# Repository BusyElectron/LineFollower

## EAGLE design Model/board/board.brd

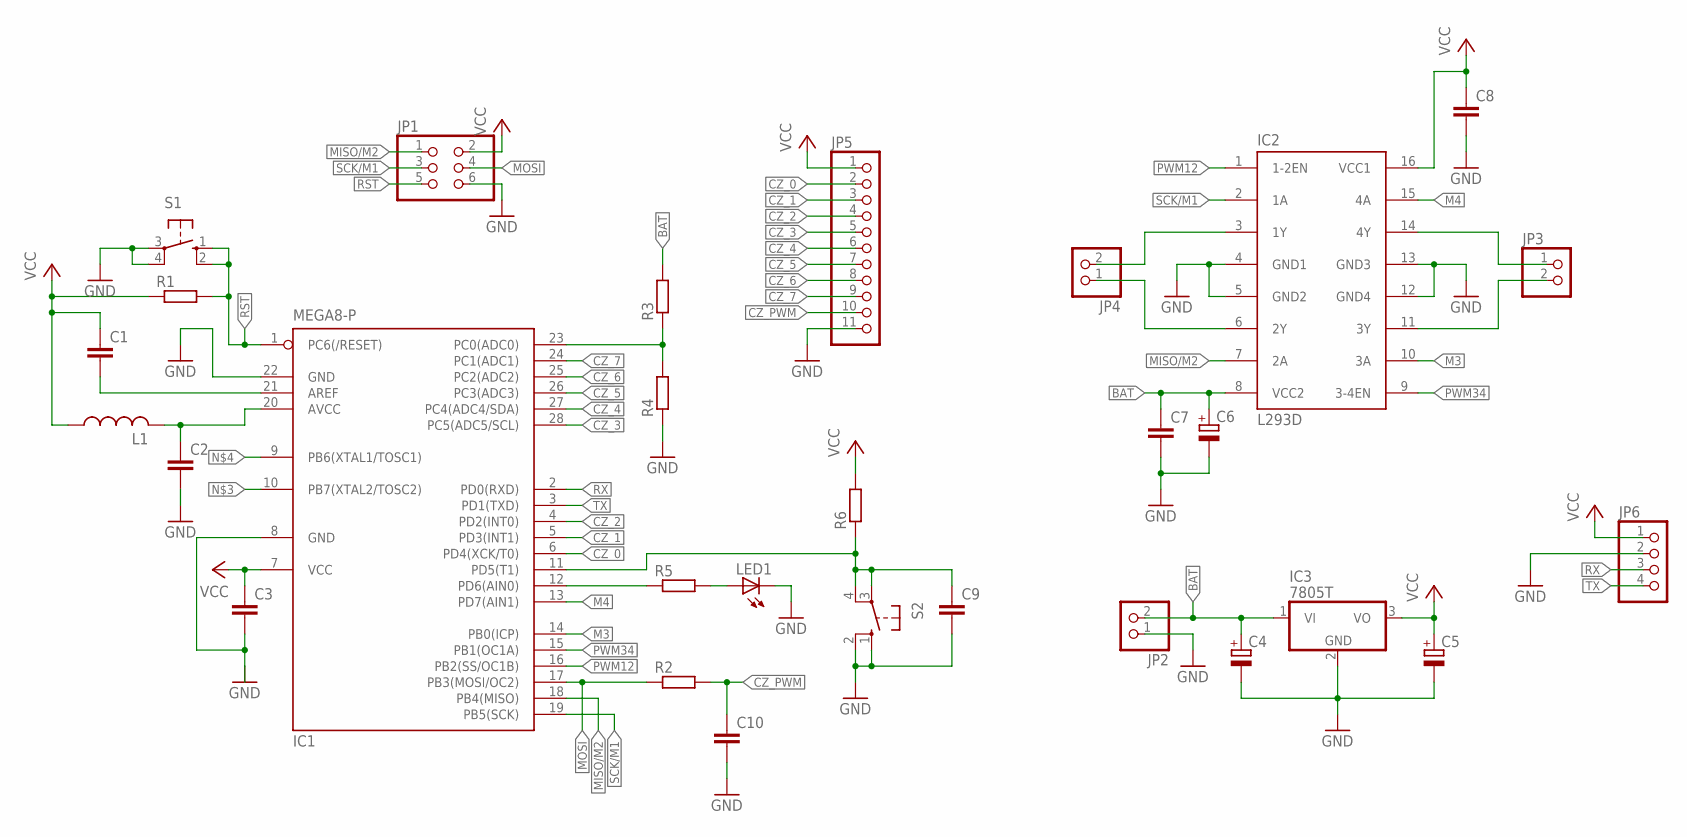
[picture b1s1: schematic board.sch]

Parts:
C1, C2, C3, C7, C8, C9: C-EU025-025X050; C025-025X050
C4, C5, C6: CPOL-EUE2-5; E2-5
C10: C-EU050-035X075; C050-035X075
IC1: MEGA8-P; DIL28-3
IC2: L293D; DIL16
IC3: 7805T; TO220H
JP1: PINHD-2X3; 2X03
JP2, JP3, JP4: PINHD-1X2; 1X02
JP5: PINHD-1X11; 1X11
JP6: PINHD-1X4; 1X04
L1: L-US0204/7; 0204/7
LED1: LED5MM
R1, R2, R3, R4, R5, R6: R-EU_0207/7; 0207/7
S1, S2: 10-XX; B3F-10XX

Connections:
BAT: C4.+, C6.+, C7.1, IC2.8 (VCC2), IC3.1 (VI), JP2.2, R3.2
CZ_0: IC1.6 (PD4(XCK/T0)), JP5.2
CZ_1: IC1.5 (PD3(INT1)), JP5.3
CZ_2: IC1.4 (PD2(INT0)), JP5.4
CZ_3: IC1.28 (PC5(ADC5/SCL)), JP5.5
CZ_4: IC1.27 (PC4(ADC4/SDA)), JP5.6
CZ_5: IC1.26 (PC3(ADC3)), JP5.7
CZ_6: IC1.25 (PC2(ADC2)), JP5.8
CZ_7: IC1.24 (PC1(ADC1)), JP5.9
CZ_PWM: C10.1, JP5.10, R2.2
GND: C2.2, C3.2, C4.-, C5.-, C6.-, C7.2, C8.2, C9.2, C10.2, IC1.8 (GND), IC1.22 (GND), IC2.4 (GND1), IC2.5 (GND2), IC2.12 (GND4), IC2.13 (GND3), IC3.2 (GND), JP1.6, JP2.1, JP5.11, JP6.2, LED1.K (C), R4.1, S1.3, S1.4 (P1), S2.1 (S), S2.2 (S1)
M3: IC1.14 (PB0(ICP)), IC2.10 (3A)
M4: IC1.13 (PD7(AIN1)), IC2.15 (4A)
MISO/M2: IC1.18 (PB4(MISO)), IC2.7 (2A), JP1.1
MOSI: IC1.17 (PB3(MOSI/OC2)), JP1.4, R2.1
unnamed: IC2.11 (3Y), JP3.2
unnamed: IC2.14 (4Y), JP3.1
unnamed: C2.1, IC1.20 (AVCC), L1.2
unnamed: LED1.A, R5.2
unnamed: IC2.3 (1Y), JP4.2
unnamed: IC2.6 (2Y), JP4.1
unnamed: C1.2, IC1.21 (AREF)
unnamed: IC1.12 (PD6(AIN0)), R5.1
unnamed: C9.1, IC1.11 (PD5(T1)), R6.1, S2.3, S2.4 (P1)
unnamed: IC1.23 (PC0(ADC0)), R3.1, R4.2
PWM12: IC1.16 (PB2(SS/OC1B)), IC2.1 (1-2EN)
PWM34: IC1.15 (PB1(OC1A)), IC2.9 (3-4EN)
RST: IC1.1 (PC6(/RESET)), JP1.5, R1.2, S1.1 (S), S1.2 (S1)
RX: IC1.2 (PD0(RXD)), JP6.3
SCK/M1: IC1.19 (PB5(SCK)), IC2.2 (1A), JP1.3
TX: IC1.3 (PD1(TXD)), JP6.4
VCC: C1.1, C3.1, C5.+, C8.1, IC1.7 (VCC), IC2.16 (VCC1), IC3.3 (VO), JP1.2, JP5.1, JP6.1, L1.1, R1.1, R6.2

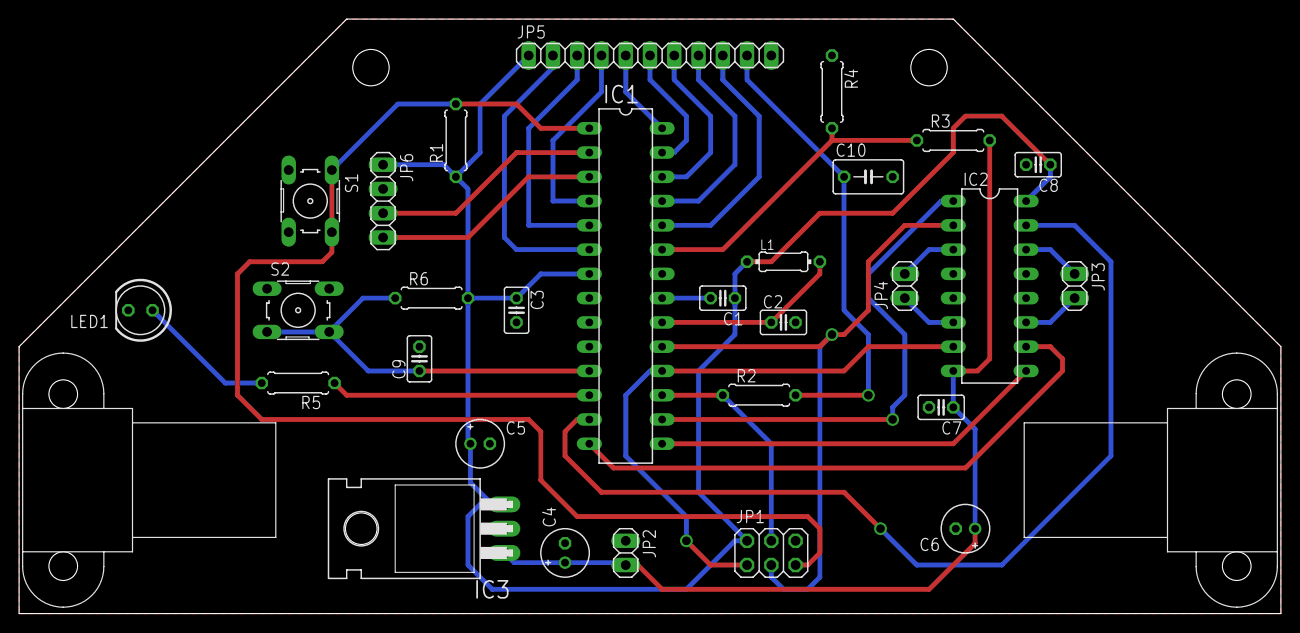
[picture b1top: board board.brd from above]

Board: 2 copper layers, 132.1 x 62.2 mm, 31 parts (0 on the bottom side), 32 nets.

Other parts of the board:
U$1, U$2: HP_NM

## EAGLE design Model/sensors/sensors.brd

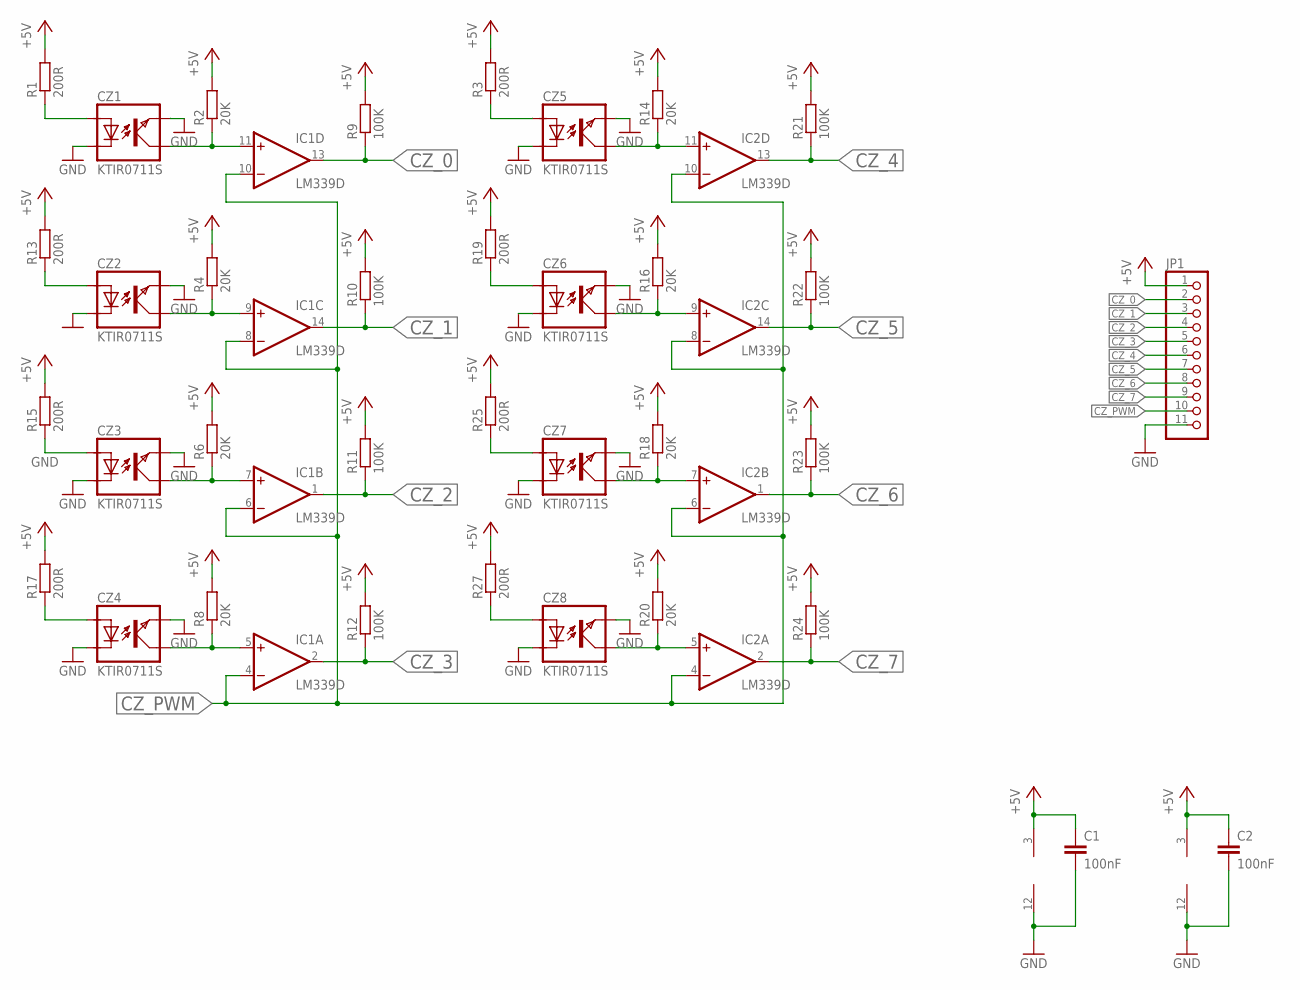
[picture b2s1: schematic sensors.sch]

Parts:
C1, C2: 100nF; C0805K
CZ1, CZ2, CZ3, CZ4, CZ5, CZ6, CZ7, CZ8: KTIR0711S; TOP
IC1, IC2: LM339D; SO14
JP1: PINHD-1X11; 1X11
R1, R3, R13, R15, R17, R19, R25, R27: 200R; R0805
R2, R4, R6, R8, R14, R16, R18, R20: 20K; R0805
R9, R10, R11, R12, R21, R22, R23, R24: 100K; R0805

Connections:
+5V: C1.1, C2.1, IC1.3 (V+), IC2.3 (V+), JP1.1, R1.2, R2.2, R3.2, R4.2, R6.2, R8.2, R9.2, R10.2, R11.2, R12.2, R13.2, R14.2, R15.2, R16.2, R17.2, R18.2, R19.2, R20.2, R21.2, R22.2, R23.2, R24.2, R25.2, R27.2
CZ_0: IC1.13 (OUT), JP1.2, R9.1
CZ_1: IC1.14 (OUT), JP1.3, R10.1
CZ_2: IC1.1 (OUT), JP1.4, R11.1
CZ_3: IC1.2 (OUT), JP1.5, R12.1
CZ_4: IC2.13 (OUT), JP1.6, R21.1
CZ_5: IC2.14 (OUT), JP1.7, R22.1
CZ_6: IC2.1 (OUT), JP1.8, R23.1
CZ_7: IC2.2 (OUT), JP1.9, R24.1
CZ_PWM: IC1.4 (-IN), IC1.6 (-IN), IC1.8 (-IN), IC1.10 (-IN), IC2.4 (-IN), IC2.6 (-IN), IC2.8 (-IN), IC2.10 (-IN), JP1.10
GND: C1.2, C2.2, CZ1.EMITER, CZ1.KATODA, CZ2.EMITER, CZ2.KATODA, CZ3.EMITER, CZ3.KATODA, CZ4.EMITER, CZ4.KATODA, CZ5.EMITER, CZ5.KATODA, CZ6.EMITER, CZ6.KATODA, CZ7.EMITER, CZ7.KATODA, CZ8.EMITER, CZ8.KATODA, IC1.12 (GND), IC2.12 (GND), JP1.11
unnamed: CZ1.KOLEKTOR, IC1.11 (+IN), R2.1
unnamed: CZ2.KOLEKTOR, IC1.9 (+IN), R4.1
unnamed: CZ3.ANODA, R15.1
unnamed: CZ1.ANODA, R1.1
unnamed: CZ5.ANODA, R3.1
unnamed: CZ3.KOLEKTOR, IC1.7 (+IN), R6.1
unnamed: CZ2.ANODA, R13.1
unnamed: CZ4.KOLEKTOR, IC1.5 (+IN), R8.1
unnamed: CZ4.ANODA, R17.1
unnamed: CZ6.ANODA, R19.1
unnamed: CZ8.ANODA, R27.1
unnamed: CZ5.KOLEKTOR, IC2.11 (+IN), R14.1
unnamed: CZ7.ANODA, R25.1
unnamed: CZ6.KOLEKTOR, IC2.9 (+IN), R16.1
unnamed: CZ7.KOLEKTOR, IC2.7 (+IN), R18.1
unnamed: CZ8.KOLEKTOR, IC2.5 (+IN), R20.1

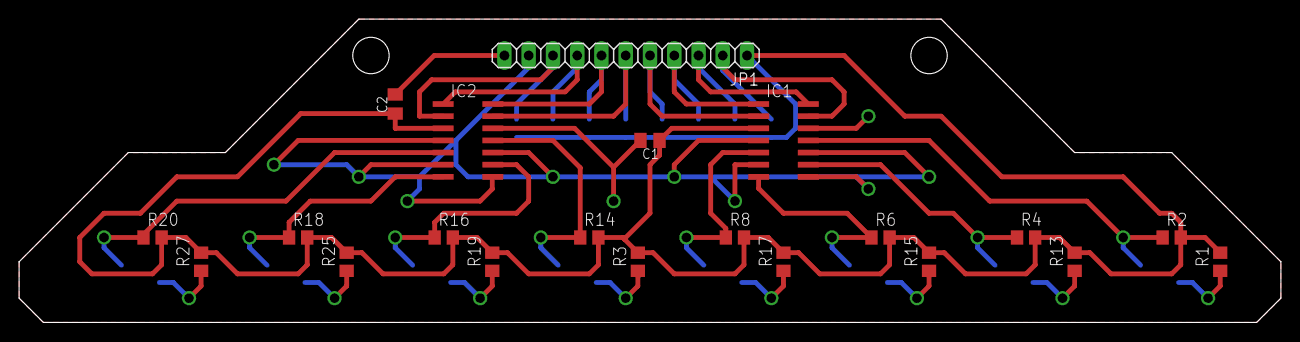
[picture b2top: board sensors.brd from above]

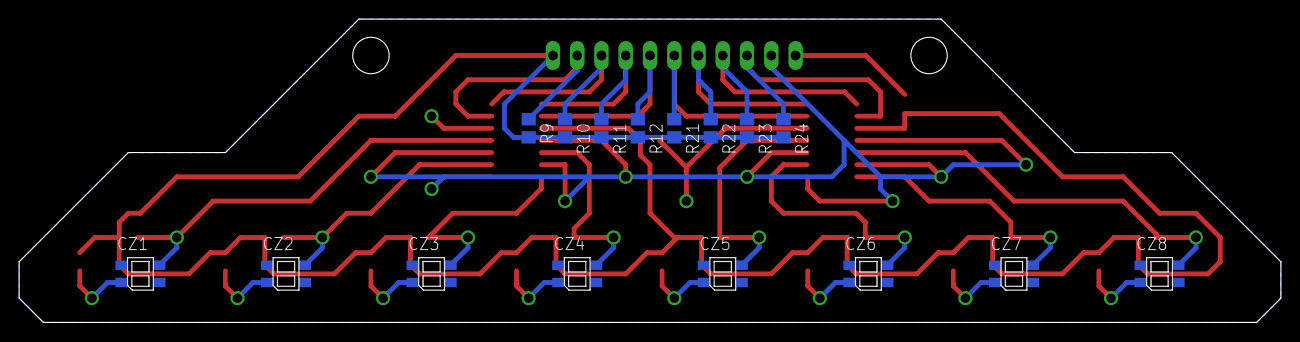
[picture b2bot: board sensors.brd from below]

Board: 2 copper layers, 132.1 x 31.8 mm, 37 parts (16 on the bottom side), 27 nets.
